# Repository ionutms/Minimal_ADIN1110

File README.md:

# Minimal_ADIN1110

## Overview

This repository contains a minimal KiCad design project for the Analog Devices ADIN1110, a robust, industrial, low-power 10BASE-T1L Ethernet MAC-PHY. The project is designed for industrial Ethernet applications and complies with the IEEE® 802.3cg-2019™ standard for long-reach, 10 Mbps Single Pair Ethernet (SPE).

## Disclaimer

> [!NOTE]
> This project is provided "as is" and without any warranty, express or implied. For more details, please see the [LICENSE](LICENSE) file.

## About the ADIN1110

The ADIN1110 from Analog Devices is a fully integrated and featured low-power 10BASE-T1L MAC-PHY. It is designed for use in industrial Ethernet applications and connects to a host controller via a 4-wire Serial Peripheral Interface (SPI). This allows for the use of lower-power processors without an integrated MAC, which helps to reduce overall system power consumption.

Key features include:

- **Integrated MAC and SPI Interface:** The ADIN1110 includes an integrated Media Access Control (MAC) that allows for direct connection to a host controller via a 4-wire Serial Peripheral Interface (SPI). This enables the use of lower-power processors without an integrated MAC, contributing to lower overall system power consumption.
- **Low Power Consumption:** The device features low power consumption, listed as 42 mW in a typical dual-supply scenario.
- **Long Cable Reach:** It supports a cable reach of up to 1700 meters.
- **Intrinsic Safety Support:** The ADIN1110 is suitable for intrinsic safety applications due to programmable transmit levels, external termination resistors, and independent receive and transmit pins.
- **Robustness:** It integrates voltage supply monitoring and power-on reset (POR) circuitry to enhance system-level robustness.
- **Package:** The ADIN1110 is available in a 40-lead, 6 mm × 6 mm Lead Frame Chip Scale Package (LFCSP).
- **Wide Temperature Range:** It operates over a wide temperature range of -40°C to +105°C.

## Project Structure

```
minimal_adin1110/
├── minimal_adin1110.kicad_sch       # Main schematic file
├── minimal_adin1110.kicad_pcb       # PCB layout file
├── minimal_adin1110.kicad_pro       # Project configuration file
├── fp-lib-table                     # Footprint library table
├── sym-lib-table                    # Symbol library table
├── project_jobs_set.kicad_jobset    # Project job settings
├── ibom.config.ini                  # Interactive BOM configuration
├── docs/                            # Documentation files
│   ├── pictures/                    # Images and photos
│   ├── schematics/                  # Schematic PDF exports
│   └── 3d_models/                   # 3D model files
└── KiCAD_Symbols_Generator/         # Submodule for symbol generation from CSV data
```

## Project Features

This design provides a minimal implementation of the ADIN1110 with the following features:

- **Power Supply:**
  - VIN: +3.3V
- **Channel Configuration:**
  - Basic protection circuits for the Ethernet twisted pair.
- **Bill of Materials (BOM):**
  - Interactive HTML BOM (`ibom.html`) for easy component identification and sourcing.
- **Libraries:**
  - Comprehensive symbol and footprint libraries integrated as a submodule.
- **3D Model:**
  - Includes a 3D model of the board for better visualization.

## Getting Started

### Prerequisites

- [KiCad EDA](https://www.kicad.org/) version 9.0 or later installed on your system
- Git (for cloning the repository and submodule management)

### Opening the Project

1. **Clone the repository** (including submodules):
   ```bash
   git clone --recursive https://github.com/ionutms/Minimal_ADIN1110.git
   ```
   
   If you've already cloned the repository without submodules, initialize them with:
   ```bash
   git submodule init
   git submodule update
   ```

2. **Open the project in KiCad**:
   - Launch KiCad
   - Click "Open Existing Project"
   - Navigate to the cloned repository folder
   - Select the `minimal_adin1110.kicad_pro` file

3. **Explore the design**:
   - Open the schematic editor to view the circuit design
   - Open the PCB editor to view the board layout
   - Review the symbol and footprint libraries used in the design

### Project Files

- **Main schematic**: `minimal_adin1110.kicad_sch` - Contains the primary circuit design with the ADIN1110 and support components
- **PCB layout**: `minimal_adin1110.kicad_pcb` - Physical board design file with proper component placement
- **Project configuration**: `minimal_adin1110.kicad_pro` - KiCad project settings

## Dependencies

This project has the following dependencies:

### 1. KiCAD Symbols Generator

This repository uses [KiCAD_Symbols_Generator](https://github.com/ionutms/KiCAD_Symbols_Generator) as a submodule for custom symbol generation.

To initialize the submodule after cloning this repository:

```bash
git submodule update --init --recursive
```

### 2. 3D Models

This project requires the [3D_Models_Vault](https://github.com/ionutms/3D_Models_Vault) repository for 3D models.

#### Setup for KiCAD 9:

1. Clone the 3D models repository:
   ```bash
   git clone https://github.com/ionutms/3D_Models_Vault.git
   ```

2. In KiCAD 9, add an environment variable:
   - Variable name: `KICAD9_3D_MODELS_VAULT`
   - Variable value: Full path to where you cloned the 3D_Models_Vault repository

## Usage

After setting up the dependencies, open the project in KiCAD 9 to access all features including the 3D models.

## Symbol Generator Submodule

This project includes the KiCAD_Symbols_Generator as a submodule, which provides tools for generating KiCad symbols from CSV data files. For more information on using this tool, see the [KiCAD_Symbols_Generator documentation](minimal_adin1110/KiCAD_Symbols_Generator/README.md).

## Documentation

The `docs` folder contains:
- Schematic PDF exports
- Images and photos of the design
- 3D model files (GLB and WRL formats)

## Visuals

The following images showcase the PCB design from different perspectives:

*Top View of the PCB*

*Side View of the PCB*

*Bottom View of the PCB*

## License

This project is licensed under the MIT License - see the [LICENSE](LICENSE) file for details.

## References

- [ADIN1110 Datasheet](https://www.analog.com/media/en/technical-documentation/data-sheets/adin1110.pdf)
- [KiCad EDA](https://www.kicad.org/)

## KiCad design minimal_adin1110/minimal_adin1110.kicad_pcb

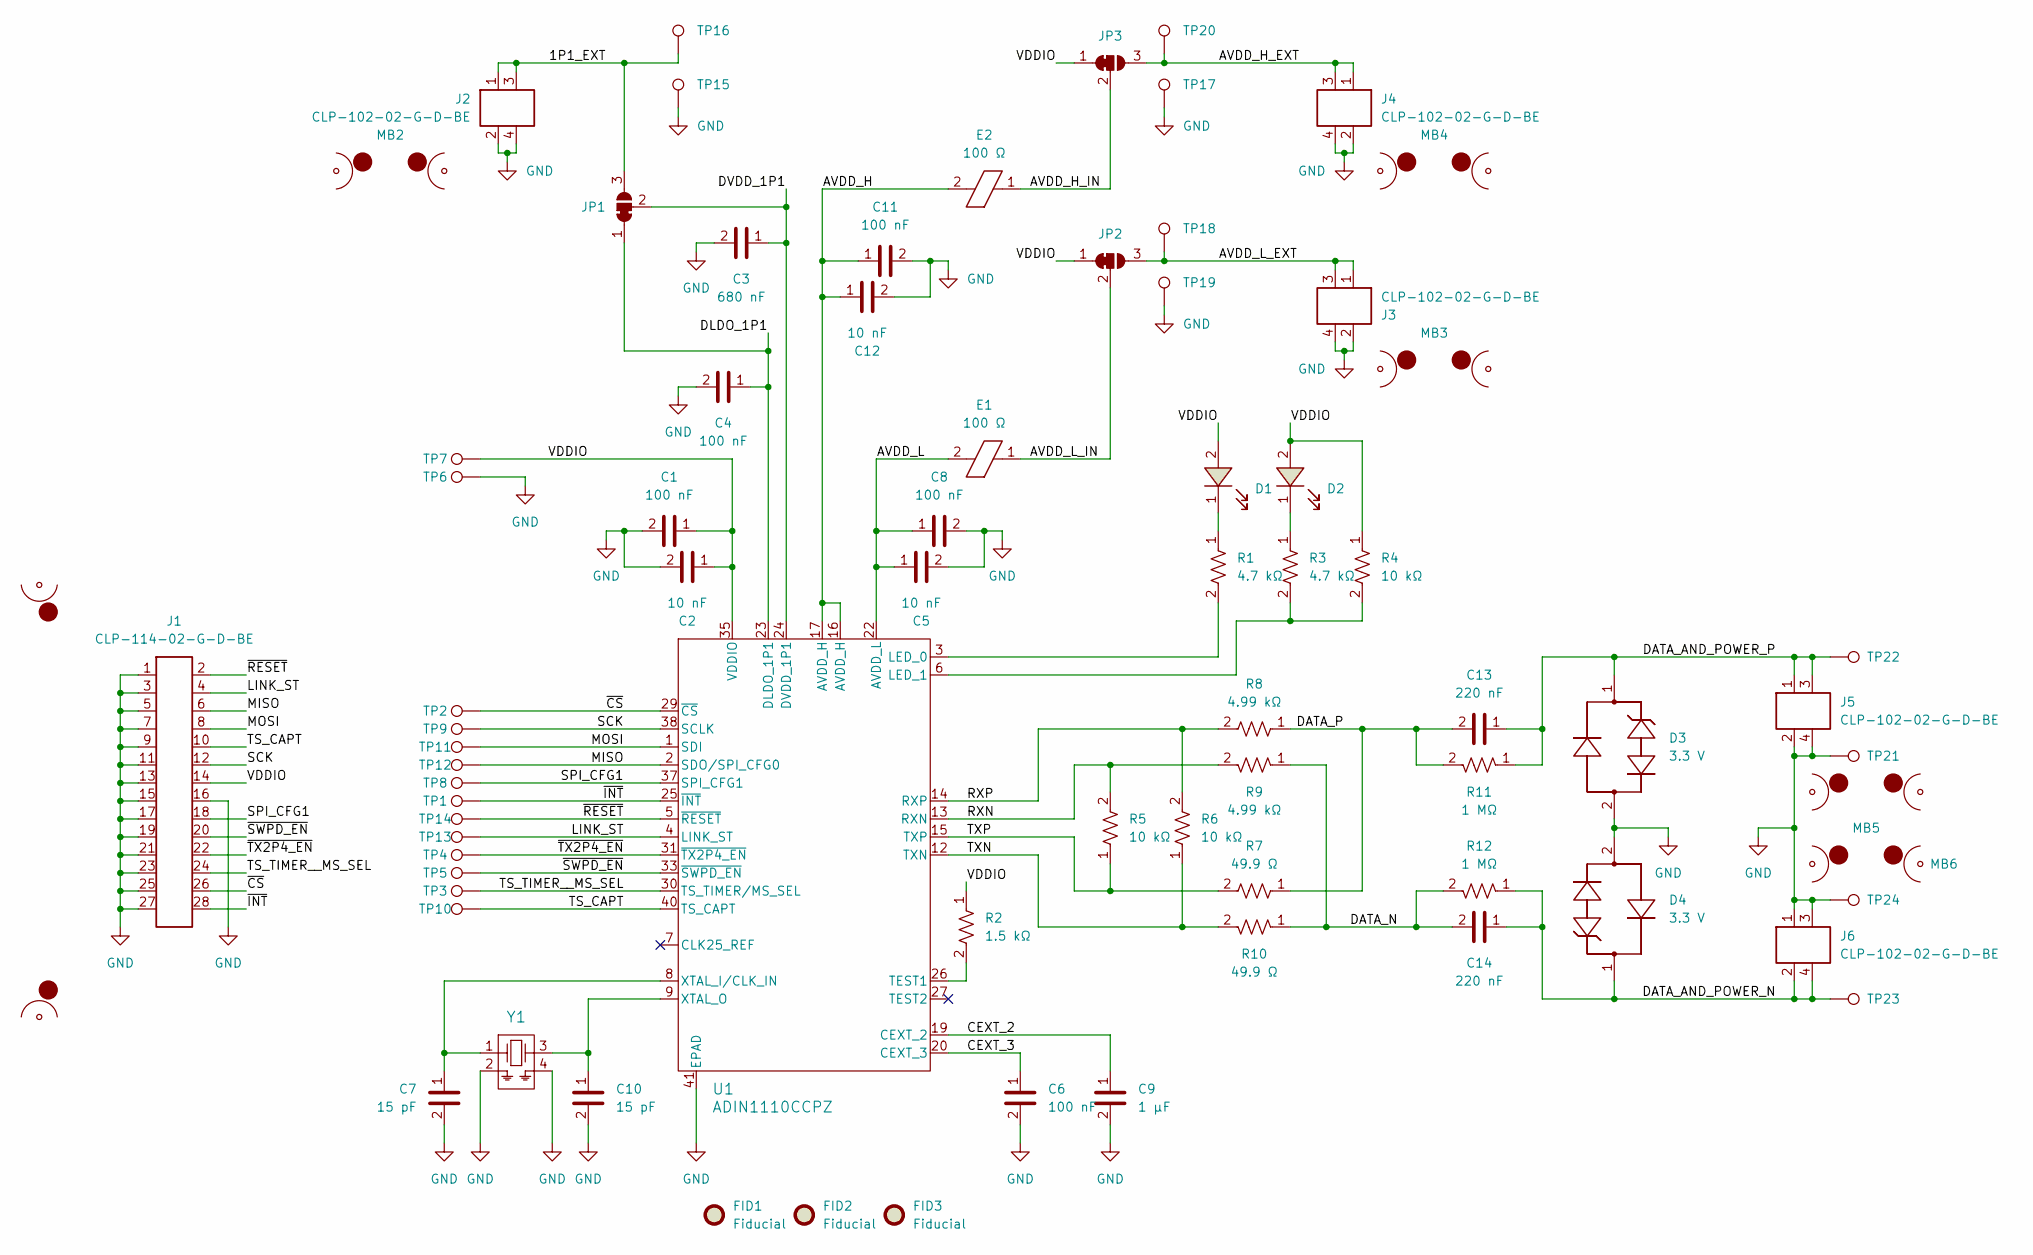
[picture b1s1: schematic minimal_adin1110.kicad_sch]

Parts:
C1, C4, C6, C8, C11: 100 nF; C_0402_1005Metric; Voltage Rating DC 50 VDC; Tolerance 10%; MPN GCM155R71H104KE02D
C2, C5, C12: 10 nF; C_0402_1005Metric; Voltage Rating DC 100 VDC; Tolerance 10%; MPN C1005X7S2A103K050BB
C3: 680 nF; C_0402_1005Metric; Voltage Rating DC 10 VDC; Tolerance 10%; MPN GCM155C71A684KE38D
C7, C10: 15 pF; C_0402_1005Metric; Voltage Rating DC 50 VDC; Tolerance 1%; MPN GCM1555C1H150FA16D
C9: 1 µF; C_0402_1005Metric; Voltage Rating DC 16 VDC; Tolerance 10%; MPN C1005X6S1C105K050BC
C13, C14: 220 nF; C_0805_2012Metric; Voltage Rating DC 16 VDC; Tolerance 5%; MPN C0805C224J1RACTU
D1, D2: 1.8 V; LED_GREEN_0402_1005Metric; MPN APHHS1005CGCK
D3, D4: 3.3 V; SOD323; MPN SP4020-01FTG
E1, E2: 100 Ω; 742792731; Tolerance ±25%; MPN 742792731
FID1, FID2, FID3: Fiducial; Fiducial_0.5mm_Mask1mm
J1: CLP-114-02-G-D-BE; Current Rating (A) 5.2; Voltage Rating (V) 300; MPN CLP-114-02-G-D-BE
J2, J3, J4, J5, J6: CLP-102-02-G-D-BE; Current Rating (A) 5.2; Voltage Rating (V) 300; MPN CLP-102-02-G-D-BE
JP1, JP2, JP3: SolderJumper_3_Open; SolderJumper-3_P1.3mm_Bridged_1_2_RoundedPad1.0x1.5mm_Numbe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
MB1: mouse-bite-midle-50mil-200mil; mouse-bite-50mil-790mil
MB2, MB3, MB4, MB5, MB6: mouse-bite-midle-50mil-200mil
R1, R3: 4.7 kΩ; R_0402_1005Metric; Voltage Rating 50V; Tolerance 5%; MPN ERJ-2GEJ472X
R2: 1.5 kΩ; R_0402_1005Metric; Voltage Rating 50V; Tolerance 1%; MPN ERJ-2RKF1501X
R4: 10 kΩ; R_0402_1005Metric; Voltage Rating 50V; Tolerance 1%; MPN ERJ-2RKF1002X
R5, R6: 10 kΩ; R_0603_1608Metric; Voltage Rating 75V; Tolerance 1%; MPN ERJ-3EKF1002V
R7, R10: 49.9 Ω; R_0603_1608Metric; Voltage Rating 75V; Tolerance 1%; MPN ERJ-3EKF49R9V
R8, R9: 4.99 kΩ; R_0603_1608Metric; Voltage Rating 75V; Tolerance 1%; MPN ERJ-3EKF4991V
R11, R12: 1 MΩ; R_0603_1608Metric; Voltage Rating 75V; Tolerance 1%; MPN ERJ-3EKF1004V
TP1, TP2, TP3, TP4, TP5, TP6, TP7, TP8, TP9, TP10, TP11, TP12, TP13, TP14, TP15, TP16, TP17, TP18, TP19, TP20, TP21, TP22, TP23, TP24: TestPoint; TestPoint_THTPad_Castelated
U1: ADIN1110CCPZ; CP-40-29_ADI; MPN ADIN1110CCPZ
Y1: 25.0000MHz; SO4_FA-128_2p0x1p6_SEC

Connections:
/1P1_EXT: J2.1, J2.3, JP1.3 (B), TP16.1
/AVDD_H: C11.1, C12.1, E2.2, U1.16 (AVDD_H), U1.17 (AVDD_H)
/AVDD_H_EXT: J4.1, J4.3, JP3.3 (B), TP20.1
/AVDD_H_IN: E2.1, JP3.2 (C)
/AVDD_L: C5.1, C8.1, E1.2, U1.22 (AVDD_L)
/AVDD_L_EXT: J3.1, J3.3, JP2.3 (B), TP18.1
/AVDD_L_IN: E1.1, JP2.2 (C)
/CEXT_2: C9.1, U1.19 (CEXT_2)
/CEXT_3: C6.1, U1.20 (CEXT_3)
/DATA_AND_POWER_N: C14.1, D4.1, J6.2, J6.4, R12.1, TP23.1
/DATA_AND_POWER_P: C13.1, D3.1, J5.1, J5.3, R11.1, TP22.1
/DATA_N: C14.2, R9.1, R10.1, R12.2
/DATA_P: C13.2, R7.1, R8.1, R11.2
/DLDO_1P1: C4.1, JP1.1 (A), U1.23 (DLDO_1P1)
/DVDD_1P1: C3.1, JP1.2 (C), U1.24 (DVDD_1P1)
/LINK_ST: J1.4, TP13.1, U1.4 (LINK_ST)
/MISO: J1.6, TP12.1, U1.2 (SDO/SPI_CFG0)
/MOSI: J1.8, TP11.1, U1.1 (SDI)
/RXN: R5.2, R9.2, U1.13 (RXN)
/RXP: R6.2, R8.2, U1.14 (RXP)
/SCK: J1.12, TP9.1, U1.38 (SCLK)
/SPI_CFG1: J1.18, TP8.1, U1.37 (SPI_CFG1)
/TS_CAPT: J1.10, TP10.1, U1.40 (TS_CAPT)
/TS_TIMER__MS_SEL: J1.24, TP3.1, U1.30 (TS_TIMER/MS_SEL)
/TXN: R6.1, R10.2, U1.12 (TXN)
/TXP: R5.1, R7.2, U1.15 (TXP)
/VDDIO: C1.1, C2.1, D1.2, D2.2, J1.14, JP2.1 (A), JP3.1 (A), R2.1, R4.1, TP7.1, U1.35 (VDDIO)
/~CS: J1.26, TP2.1, U1.29 (~CS)
/~INT: J1.28, TP1.1, U1.25 (~INT)
/~RESET: J1.2, TP14.1, U1.5 (~RESET)
/~SWPD_EN: J1.20, TP5.1, U1.33 (~SWPD_EN)
/~TX2P4_EN: J1.22, TP4.1, U1.31 (~TX2P4_EN)
GND: C1.2, C2.2, C3.2, C4.2, C5.2, C6.2, C7.2, C8.2, C9.2, C10.2, C11.2, C12.2, D3.2, D4.2, J1.1, J1.3, J1.5, J1.7, J1.9, J1.11, J1.13, J1.15, J1.16, J1.17, J1.19, J1.21, J1.23, J1.25, J1.27, J2.2, J2.4, J3.2, J3.4, J4.2, J4.4, J5.2, J5.4, J6.1, J6.3, TP6.1, TP15.1, TP17.1, TP19.1, TP21.1, TP24.1, U1.41 (EPAD), Y1.2, Y1.4
unnamed: D1.1, R1.1
unnamed: D2.1, R3.1
unnamed: R1.2, U1.3 (LED_0)
unnamed: R3.2, R4.2, U1.6 (LED_1)
unnamed: R2.2, U1.26 (TEST1)
unnamed: C7.1, U1.8 (XTAL_I/CLK_IN), Y1.1
unnamed: C10.1, U1.9 (XTAL_O), Y1.3

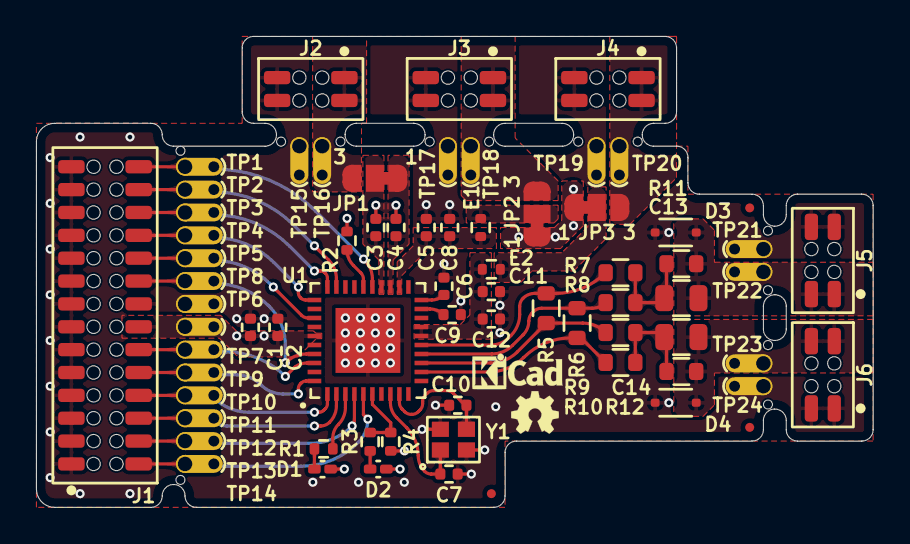
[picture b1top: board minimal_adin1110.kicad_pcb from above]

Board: 4 copper layers, 46.5 x 26.2 mm, 76 parts (0 on the bottom side), 40 nets.

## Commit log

2025-02-03 Add initial KiCad project files for minimal_adin1110
2025-02-03 Add submodule for KiCAD Symbol Generator
2025-02-04 Update KiCAD Symbol Generator submodule and add symbol and footprint library tables
2025-02-05 Add ibom.config.ini for minimal_adin1110 configuration settings
2025-02-05 Add schematic PDF for minimal_adin1110 project
2025-02-05 Add WRL 3D model for minimal_adin1110
2025-02-05 Add VRML file reference for minimal_adin1110 project
2025-02-05 Backup
2025-02-07 Update component blacklist in ibom.config.ini to include JP* and MB*
2025-02-07 Add UNITED_MOUSE_BITES_DATA_BASE library to sym-lib-table
2025-02-08 Add GLB 3D model
2025-02-12 Minor changes
2025-02-28 Update component blacklist and add new libraries to symbol and footprint tables
2025-03-04 Update minimal_adin1110 GLB file
2025-03-07 Update subproject commit for KiCAD Symbol Generator
2025-03-08 Update KiCAD subproject commit and adjust pad dimensions
2025-03-10 Update subproject commit for minimal_adin1110 and refresh GLB file
2025-03-16 Remove KiCAD Symbol Generator submodule and associated configuration
2025-03-16 Add KiCAD Symbols Generator submodule and configuration
2025-03-16 Update minimal_adin1110 configuration and library paths for KiCAD Symbols Generator
2025-03-18 Switch to KiCad 9
2025-03-19 Add .log files to .gitignore
2025-03-19 Add project job set configuration for minimal_adin1110
2025-03-19 Add minimal_adin1110 side image
2025-03-19 Update project job set for minimal_adin1110 with new export command and settings
2025-03-19 Update minimal_adin1110 assets with new GLB and side image files
2025-03-20 Add new render command to project job set for minimal_adin1110
2025-03-20 Update subproject reference for KiCAD Symbols Generator
2025-03-20 Add new assets and update project configuration for minimal_adin1110
2025-03-21 Update project job set for minimal_adin1110 with new rendering commands and output paths
2025-03-21 Remove outdated images and add new 3D model and picture assets for minimal_adin1110
2025-03-22 Update README.md to include project dependencies and setup instructions
2025-04-11 development backup
2025-04-11 Update images and 3d models
2025-04-11 Revert "Update images and 3d models"
    This reverts commit 70a4131f5101a5759838f3214f5333fe693e777d.
2025-04-11 Revert "development backup"
    This reverts commit 9283c747e1c3676efe85313f236ce4507e137f4e.
2025-04-12 Adjust rendering commands for side and top images in job settings
2025-04-12 Update 3D model and picture assets for minimal_adin1110
2025-04-15 Update subproject commit reference for KiCAD Symbols Generator
2025-04-17 Update KiCad documentation (schematics and PCB renders)
2025-04-18 Update Docker image in workflow and remove obsolete schematic and image files for minimal_adin1110
2025-04-18 Update Docker image for KiCad to version 9.0 in workflow
2025-04-18 Update subproject commit for KiCAD Symbols Generator
2025-04-18 Update trigger branch for KiCad documentation generation workflow
2025-04-18 Enhance GitHub Actions workflow for KiCad documentation generation by adding permissions, improving branch handling, and ensuring proper output restoration and commit processes.
2025-04-18 Update GitHub Actions workflow for KiCad documentation generation
2025-04-18 Add zoom factor input for PCB 3D view rendering in workflow
2025-04-18 Refactor zoom factor handling in PCB 3D view rendering step
2025-04-18 Refactor zoom factor handling in KiCad job workflow to use environment variable
2025-04-18 Update default zoom factor in KiCad job workflow and simplify zoom factor handling
2025-04-18 Add configuration file for default zoom factor and update job workflow to use it
2025-04-24 Refactor workflow to improve handling of KiCad project files and outputs
2025-04-24 Update KiCad documentation for minimal_adin1110 (schematics and PCB renders)
2025-04-24 Add detailed view configuration to KiCad settings
2025-04-24 Remove obsolete schematic and image files for minimal_adin1110
2025-04-24 Update KiCad configuration for improved view settings
2025-04-24 Update KiCad configuration for side view settings
2025-05-24 Add GitHub Actions workflow to generate KiCad 3D models
2025-05-25 Update workflow trigger branch for KiCad 3D models generation
2025-08-18 Add bottom view rendering support to KiCad workflow
2025-08-22 Update GitHub workflow files for KiCad jobs and 3D models
2025-08-29 Update GitHub workflows for KiCad models and jobs
2025-09-02 backup and cleanup
2025-09-02 docs: update README.md
2025-10-05 chore: update workflows from central repository
2025-10-05 chore: update workflows and kicad config from central repository
2025-10-26 Update kicad-config workflow settings
